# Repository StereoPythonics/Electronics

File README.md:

# Electronics
Schematics and PCBs for my electronics projects.

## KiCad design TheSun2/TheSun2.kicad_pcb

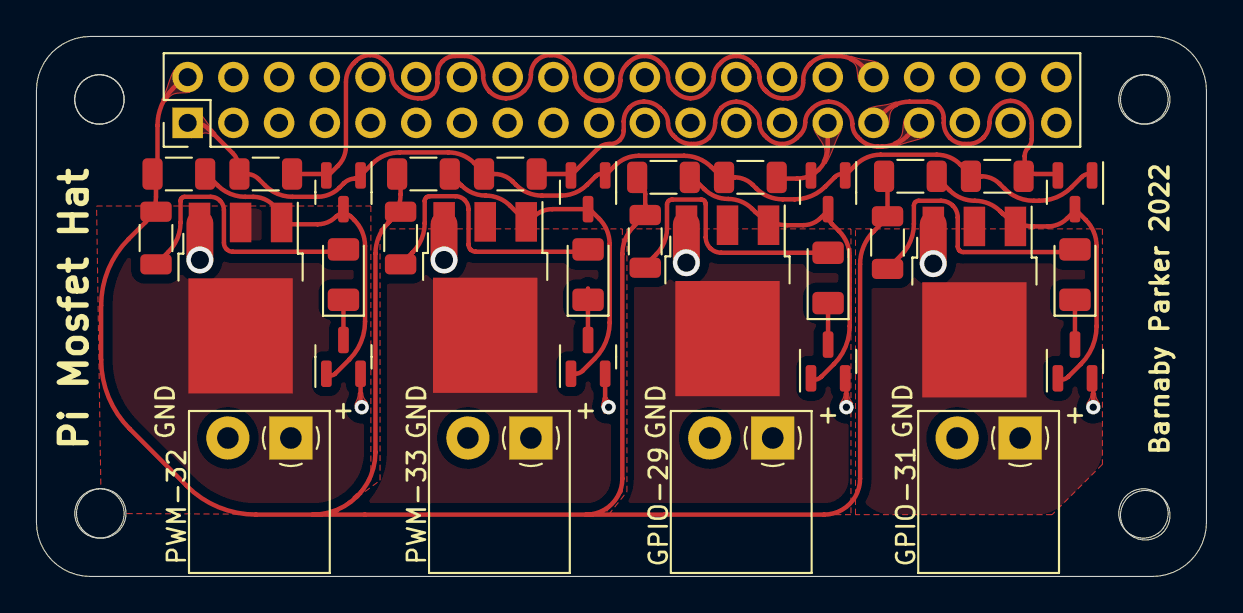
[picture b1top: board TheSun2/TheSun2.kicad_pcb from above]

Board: 2 copper layers, 65.0 x 30.0 mm, 33 parts (0 on the bottom side), 23 nets.

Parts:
D1, D2, D3, D4: LED; LED_1206_3216Metric
GPIO-29, GPIO-31: Screw_Terminal_01x02; TerminalBlock_4Ucon_1x02_P3.50mm_Horizontal
J5: Conn_02x20_Odd_Even; PinHeader_2x20_P2.54mm_Vertical
PWM-32, PWM-33: Screw_Terminal_01x02; TerminalBlock_4Ucon_1x02_P3.50mm_Horizontal
Q1, Q2, Q3, Q4: IRLR7843; TO-252-3_TabPin2
R1, R3, R4, R6, R7, R9, R10, R12: 10K; R_1206_3216Metric
R2, R5, R8, R11: 500R; R_1206_3216Metric
U1, U2, U3, U4, U5, U6, U7, U8: 2N7002H; SOT-23

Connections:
3.3v: J5.1, R1.1, R4.1, R7.1, R10.1, U1.1 (G), U2.1 (G), U5.1 (G), U6.1 (G)
5v: J5.2, R2.1, R3.2, R5.1, R6.2, R8.1, R9.2, R11.1, R12.2
/GPIO-29: J5.29, R4.2, U2.2 (S)
/GPIO-31: J5.31, R10.2, U6.2 (S)
/PWM-32: J5.32, R1.2, U1.2 (S)
/PWM-33: J5.33, R7.2, U5.2 (S)
GND: GPIO-29.2, GPIO-31.2, J5.6, J5.9, J5.14, J5.20, J5.25, J5.30, J5.34, J5.39, PWM-32.2, PWM-33.2, Q1.3 (S), Q2.3 (S), Q3.3 (S), Q4.3 (S), U3.2 (S), U4.2 (S), U7.2 (S), U8.2 (S)
unnamed: D1.1 (K), U3.3 (D)
unnamed: D1.2 (A), R2.2
unnamed: D2.1 (K), U4.3 (D)
unnamed: D2.2 (A), R5.2
unnamed: D3.1 (K), U7.3 (D)
unnamed: D3.2 (A), R8.2
unnamed: D4.1 (K), U8.3 (D)
unnamed: D4.2 (A), R11.2
unnamed: PWM-32.1, Q1.2 (D)
unnamed: GPIO-29.1, Q2.2 (D)
unnamed: PWM-33.1, Q3.2 (D)
unnamed: GPIO-31.1, Q4.2 (D)
unnamed: Q1.1 (G), R3.1, U1.3 (D), U3.1 (G)
unnamed: Q2.1 (G), R6.1, U2.3 (D), U4.1 (G)
unnamed: Q3.1 (G), R9.1, U5.3 (D), U7.1 (G)
unnamed: Q4.1 (G), R12.1, U6.3 (D), U8.1 (G)

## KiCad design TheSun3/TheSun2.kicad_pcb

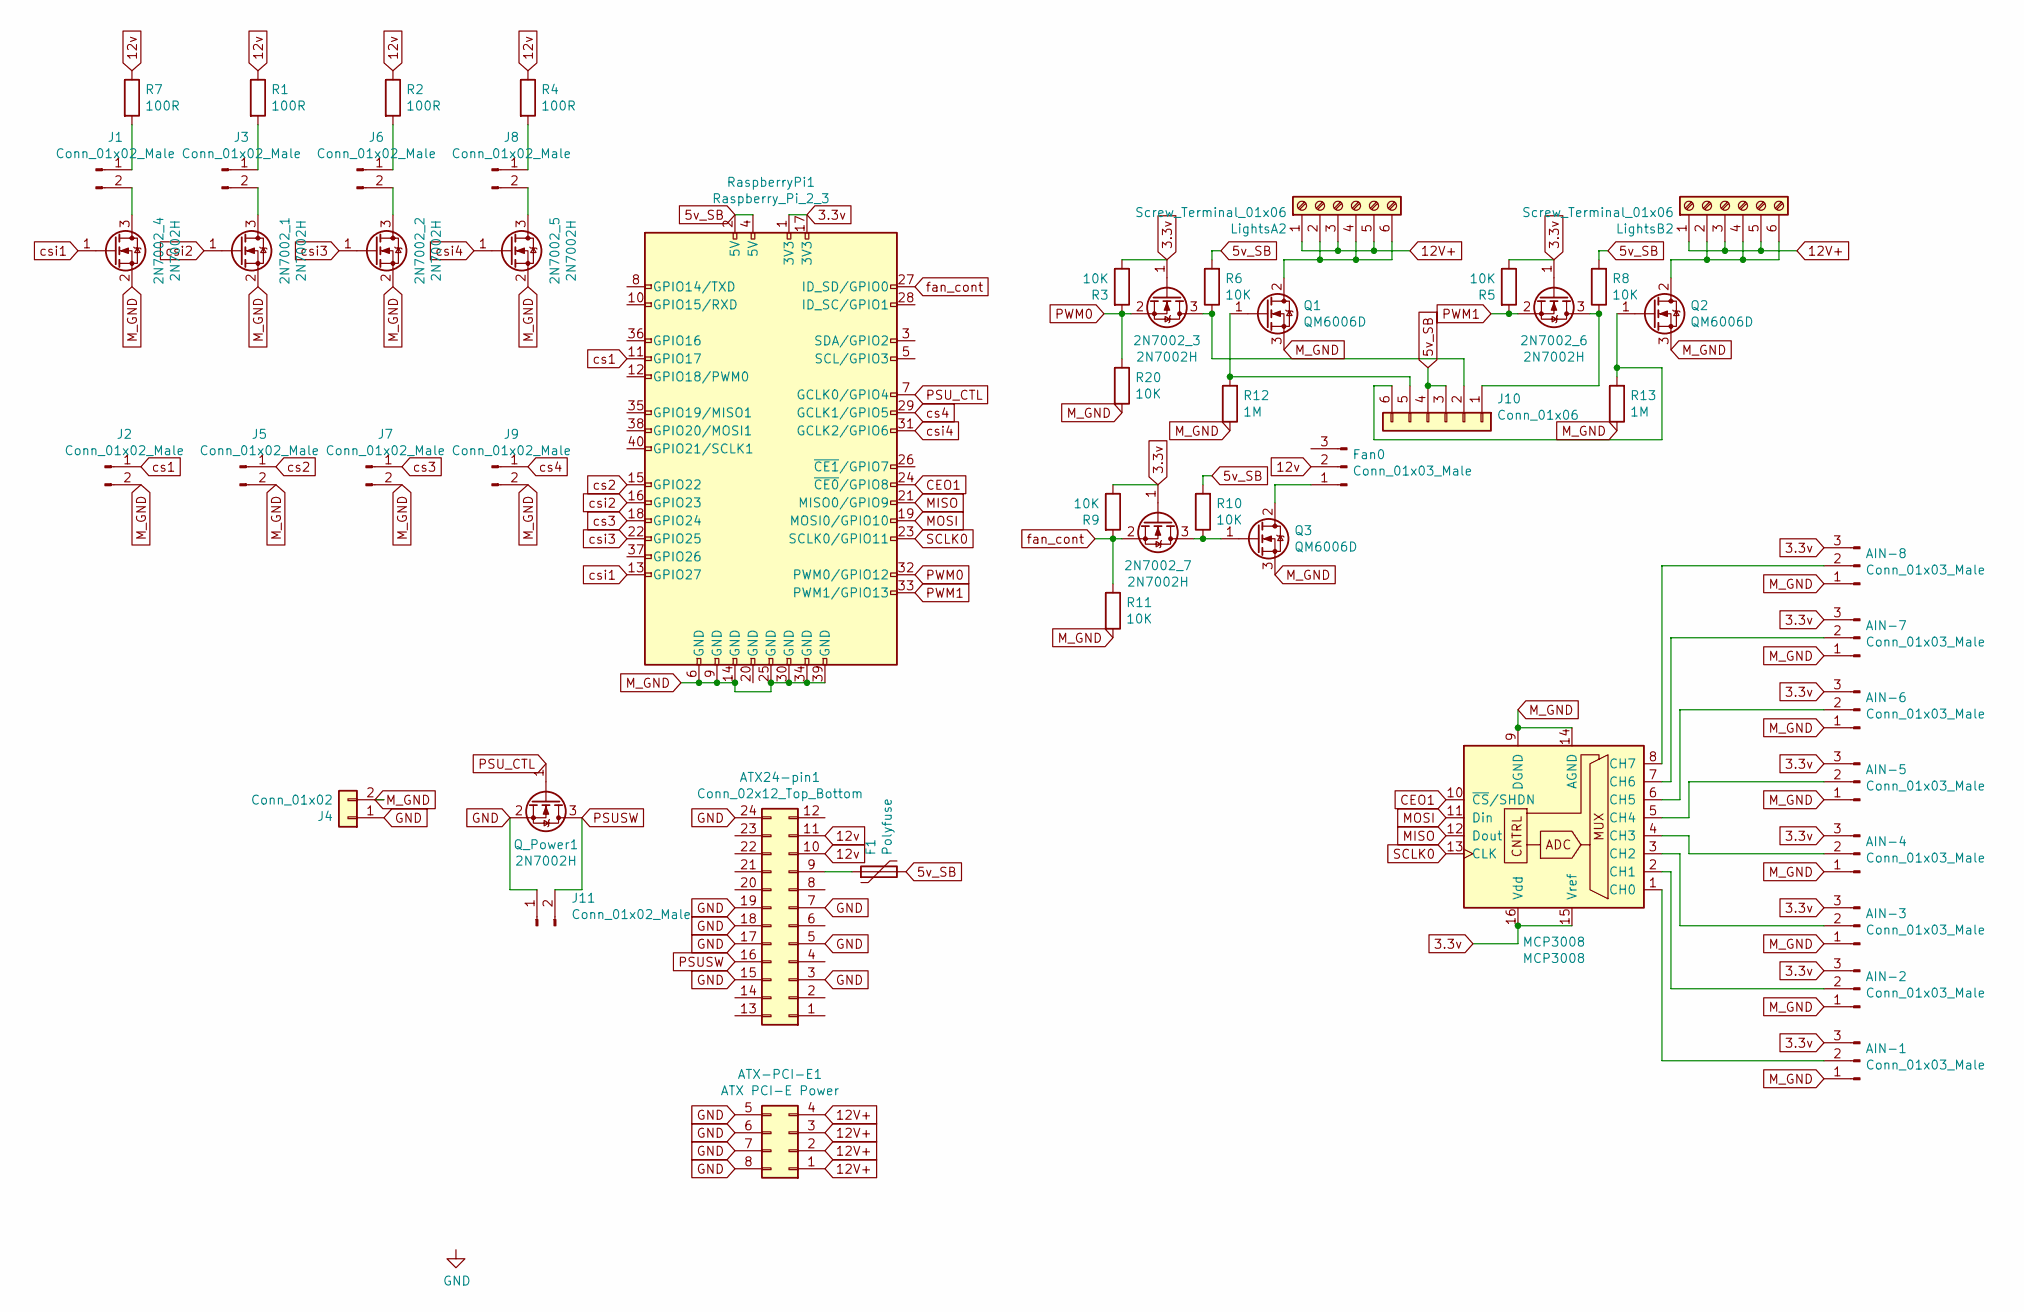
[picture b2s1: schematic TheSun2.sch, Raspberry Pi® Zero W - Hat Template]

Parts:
2N7002_1, 2N7002_2, 2N7002_3, 2N7002_4, 2N7002_5, 2N7002_6, 2N7002_7: 2N7002H; SOT-23
AIN-1, AIN-2, AIN-3, AIN-4, AIN-5, AIN-6, AIN-7, AIN-8: Conn_01x03_Male; PinHeader_1x03_P2.54mm_Vertical
ATX24-pin1: Conn_02x12_Top_Bottom; ATX_24pin
ATX-PCI-E1: ATX PCI-E Power; Molex_PCI_E_8Pin
F1: Polyfuse; R_1206_3216Metric_Pad1.30x1.75mm_HandSolder
Fan0: Conn_01x03_Male; PinHeader_1x03_P2.54mm_Vertical
J1, J2, J3, J5, J6, J7, J8, J9, J11: Conn_01x02_Male; PinHeader_1x02_P2.54mm_Vertical
J4: Conn_01x02; AMASS_XT60-M_1x02_P7.20mm_Vertical
J10: Conn_01x06; PinSocket_2x03_P2.54mm_Vertical
LightsA2: Screw_Terminal_01x06; PhoenixContact_MCV_1,5_6-G-3.81_1x06_P3.81mm_Vertical
LightsB2: Screw_Terminal_01x06; PhoenixContact_MCV_1,5_6-G-3.81_1x06_P3.81mm_Vertical
MCP3008: MCP3008; SOIC-16_3.9x9.9mm_P1.27mm
Q1, Q2, Q3: QM6006D; TO-252-2
Q_Power1: 2N7002H; SOT-23
R1, R2, R4, R7: 100R; R_1206_3216Metric_Pad1.30x1.75mm_HandSolder
R3, R5, R6, R8, R9, R10, R11, R20: 10K; R_1206_3216Metric_Pad1.30x1.75mm_HandSolder
R12, R13: 1M; R_1206_3216Metric_Pad1.30x1.75mm_HandSolder
RaspberryPi1: Raspberry_Pi_2_3; PinHeader_2x20_P2.54mm_Vertical

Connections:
3.3v: 2N7002_3.1 (G), 2N7002_6.1 (G), 2N7002_7.1 (G), AIN-1.3, AIN-2.3, AIN-3.3, AIN-4.3, AIN-5.3, AIN-6.3, AIN-7.3, AIN-8.3, MCP3008.15 (Vref), MCP3008.16 (Vdd), R3.1, R5.1, R9.1, RaspberryPi1.1 (3V3), RaspberryPi1.17 (3V3)
5v_SB: F1.2, J10.3, J10.4, R6.2, R8.2, R10.2, RaspberryPi1.2 (5V), RaspberryPi1.4 (5V)
12V+: ATX-PCI-E1.1, ATX-PCI-E1.2, ATX-PCI-E1.3, ATX-PCI-E1.4, LightsA2.1, LightsA2.3, LightsA2.5, LightsB2.1, LightsB2.3, LightsB2.5
12v: ATX24-pin1.10, ATX24-pin1.11, Fan0.2, R1.1, R2.1, R4.1, R7.1
CEO1: MCP3008.10 (~CS~/SHDN), RaspberryPi1.24 (~CE0~/GPIO8)
GND: ATX24-pin1.3, ATX24-pin1.5, ATX24-pin1.7, ATX24-pin1.15, ATX24-pin1.17, ATX24-pin1.18, ATX24-pin1.19, ATX24-pin1.24, ATX-PCI-E1.5, ATX-PCI-E1.6, ATX-PCI-E1.7, ATX-PCI-E1.8, J4.1, J11.1, Q_Power1.2 (S); also elsewhere on the board
MISO: MCP3008.12 (Dout), RaspberryPi1.21 (MISO0/GPIO9)
MOSI: MCP3008.11 (Din), RaspberryPi1.19 (MOSI0/GPIO10)
M_GND: 2N7002_1.2 (S), 2N7002_2.2 (S), 2N7002_4.2 (S), 2N7002_5.2 (S), AIN-1.1, AIN-2.1, AIN-3.1, AIN-4.1, AIN-5.1, AIN-6.1, AIN-7.1, AIN-8.1, J2.2, J4.2, J5.2, J7.2, J9.2, MCP3008.9 (DGND), MCP3008.14 (AGND), Q1.3 (S), Q2.3 (S), Q3.3 (S), R11.2, R12.1, R13.1, R20.2, RaspberryPi1.6 (GND), RaspberryPi1.9 (GND), RaspberryPi1.14 (GND), RaspberryPi1.25 (GND), RaspberryPi1.30 (GND), RaspberryPi1.34 (GND), RaspberryPi1.39 (GND)
unnamed: 2N7002_1.3 (D), J3.2
unnamed: 2N7002_2.3 (D), J6.2
unnamed: 2N7002_3.3 (D), J10.2, R6.1
unnamed: 2N7002_4.3 (D), J1.2
unnamed: 2N7002_5.3 (D), J8.2
unnamed: 2N7002_6.3 (D), J10.1, R8.1
unnamed: 2N7002_7.3 (D), Q3.1 (G), R10.1
unnamed: AIN-1.2, MCP3008.1 (CH0)
unnamed: AIN-2.2, MCP3008.2 (CH1)
unnamed: AIN-3.2, MCP3008.3 (CH2)
unnamed: AIN-4.2, MCP3008.4 (CH3)
unnamed: AIN-5.2, MCP3008.5 (CH4)
unnamed: AIN-6.2, MCP3008.6 (CH5)
unnamed: AIN-7.2, MCP3008.7 (CH6)
unnamed: AIN-8.2, MCP3008.8 (CH7)
unnamed: ATX24-pin1.9, F1.1
unnamed: Fan0.1, Q3.2 (D)
unnamed: J1.1, R7.2
unnamed: J3.1, R1.2
unnamed: J6.1, R2.2
unnamed: J8.1, R4.2
unnamed: J10.5, Q1.1 (G), R12.2
unnamed: J10.6, Q2.1 (G), R13.2
unnamed: LightsA2.2, LightsA2.4, LightsA2.6, Q1.2 (D)
unnamed: LightsB2.2, LightsB2.4, LightsB2.6, Q2.2 (D)
PSUSW: ATX24-pin1.16, J11.2, Q_Power1.3 (D); also elsewhere on the board
PSU_CTL: Q_Power1.1 (G), RaspberryPi1.7 (GCLK0/GPIO4)
PWM0: 2N7002_3.2 (S), R3.2, R20.1, RaspberryPi1.32 (PWM0/GPIO12)
PWM1: 2N7002_6.2 (S), R5.2, RaspberryPi1.33 (PWM1/GPIO13)
SCLK0: MCP3008.13 (CLK), RaspberryPi1.23 (SCLK0/GPIO11)
cs1: J2.1, RaspberryPi1.11 (GPIO17)
cs2: J5.1, RaspberryPi1.15 (GPIO22)
cs3: J7.1, RaspberryPi1.18 (GPIO24)
cs4: J9.1, RaspberryPi1.29 (GCLK1/GPIO5)
csi1: 2N7002_4.1 (G), RaspberryPi1.13 (GPIO27)
csi2: 2N7002_1.1 (G), RaspberryPi1.16 (GPIO23)
csi3: 2N7002_2.1 (G), RaspberryPi1.22 (GPIO25)
csi4: 2N7002_5.1 (G), RaspberryPi1.31 (GCLK2/GPIO6)
fan_cont: 2N7002_7.2 (S), R9.2, R11.1, RaspberryPi1.27 (ID_SD/GPIO0)

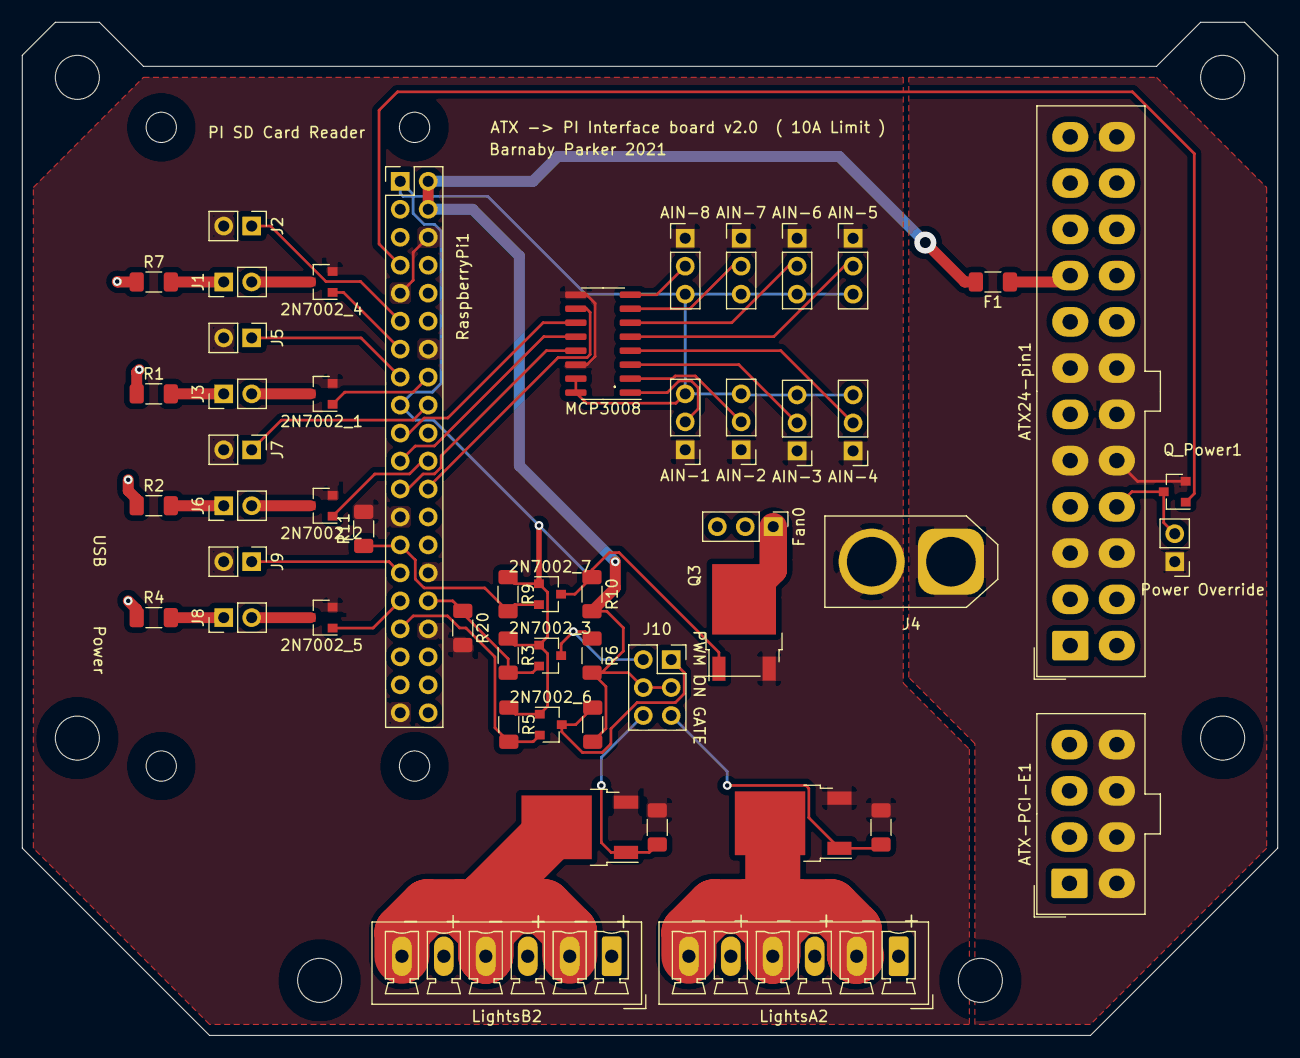
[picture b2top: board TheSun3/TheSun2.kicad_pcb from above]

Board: 2 copper layers, 114.0 x 92.0 mm, 52 parts (0 on the bottom side), 48 nets.

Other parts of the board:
Power Override: Conn_01x02_Male; PinHeader_1x02_P2.54mm_Vertical

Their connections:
GND: Power Override.1; also elsewhere on the board
PSUSW: Power Override.2; also elsewhere on the board

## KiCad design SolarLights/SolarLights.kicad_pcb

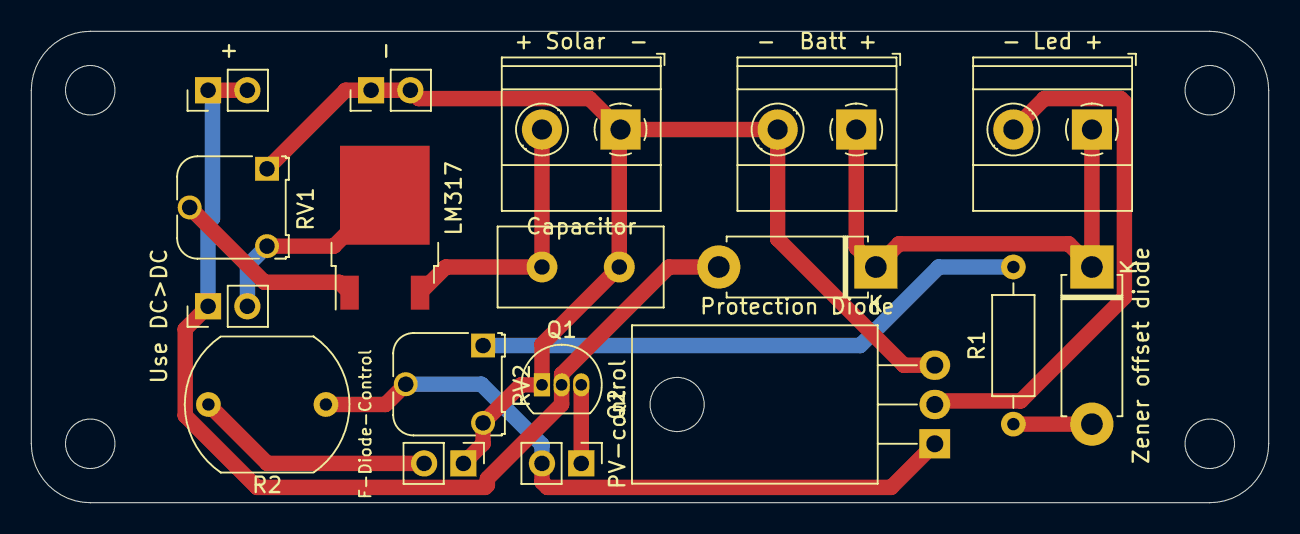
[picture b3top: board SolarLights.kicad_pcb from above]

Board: 2 copper layers, 80.0 x 30.5 mm, 22 parts (0 on the bottom side), 12 nets.

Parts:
 : MountingHole_3.2mm_M3
 #2,  #3,  #4: MountingHole_3.2mm_M3
+: dc->dc +; PinHeader_1x02_P2.54mm_Vertical
+ Solar  -: C; C_Disc_D10.5mm_W5.0mm_P5.00mm
-: dc->dc -; PinHeader_1x02_P2.54mm_Vertical
-  Batt +: Battery Terminal; TerminalBlock_Phoenix_MKDS-1,5-2-5.08_1x02_P5.08mm_Horizont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
- Led +: Led Terminal; TerminalBlock_Phoenix_MKDS-1,5-2-5.08_1x02_P5.08mm_Horizont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
Capacitor: Solar; TerminalBlock_Phoenix_MKDS-1,5-2-5.08_1x02_P5.08mm_Horizont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
F-Diode-Control: Jumper; PinHeader_1x02_P2.54mm_Vertical
LM317: LM317_TO-252; TO-252-2
PV-control: Jumper; PinHeader_1x02_P2.54mm_Vertical
Protection Diode: D; D_5W_P10.16mm_Horizontal
Q1: 2N7000; TO-92_Inline
Q2: IRLZ44N; TO-220-3_Horizontal_TabDown
R1: R; R_Axial_DIN0207_L6.3mm_D2.5mm_P10.16mm_Horizontal
R2: LDR03; R_LDR_10x8.5mm_P7.6mm_Vertical
RV1, RV2: R_POT; Potentiometer_Runtron_RM-065_Vertical
Use DC>DC: Jumper; PinHeader_1x02_P2.54mm_Vertical
Zener offset diode: D_Zener; D_5W_P10.16mm_Horizontal

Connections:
unnamed: + Solar -.1, Capacitor.2, LM317.3
unnamed: + Solar -.2, -.1, -.2, - Batt +.2, Capacitor.1, F-Diode-Control.1, Q1.1, Q2.3, RV1.1, RV2.3
unnamed: - Batt +.1, - Led +.1, Protection Diode.1, Zener offset diode.1
unnamed: +.1, +.2, Protection Diode.2, Q1.2, Use DC>DC.1
unnamed: R1.1, Zener offset diode.2
unnamed: LM317.2, RV1.3, Use DC>DC.2
unnamed: - Led +.2, Q2.2
unnamed: F-Diode-Control.2, R2.2
unnamed: PV-control.1, Q1.3
unnamed: PV-control.2, Q2.1, R2.1, RV2.2
unnamed: R1.2, RV2.1
unnamed: LM317.1, RV1.2

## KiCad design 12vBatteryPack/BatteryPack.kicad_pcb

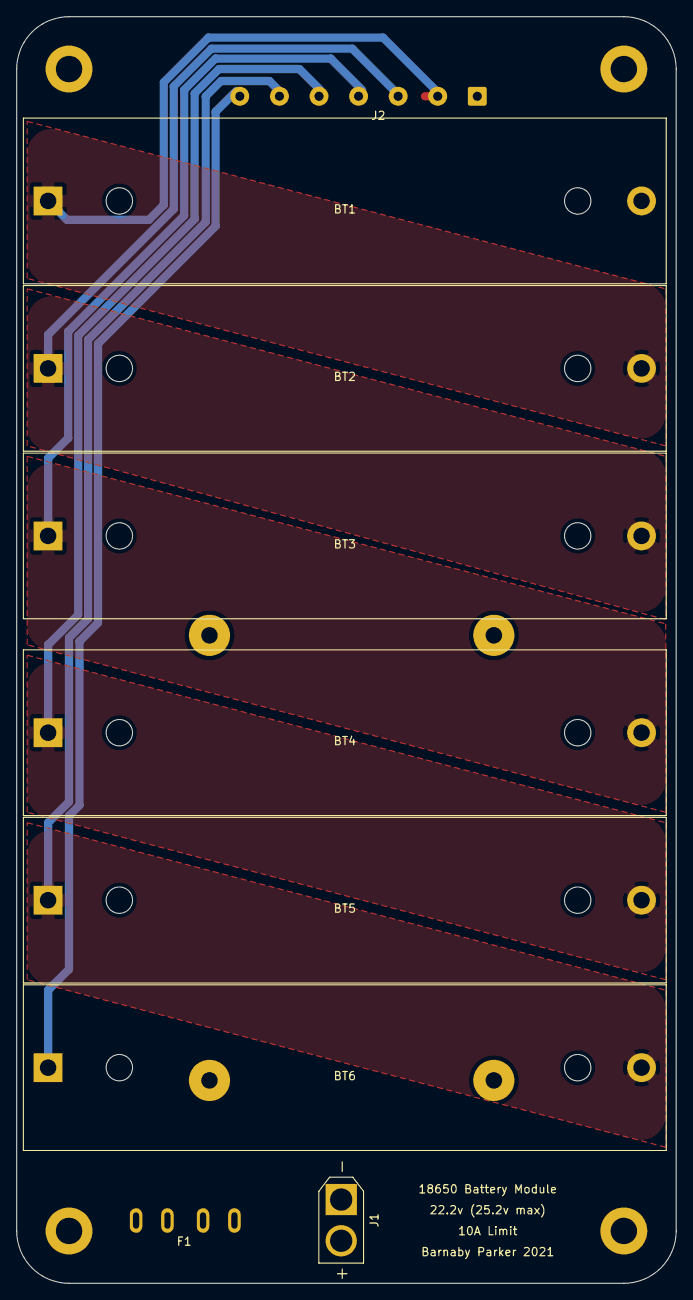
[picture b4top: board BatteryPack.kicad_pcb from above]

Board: 2 copper layers, 80.0 x 153.7 mm, 10 parts (1 on the bottom side), 9 nets.

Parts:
BT1, BT2, BT3, BT4, BT5, BT6: Battery_Cell; BatteryHolder_MPD_BH-18650-PC2
F1: Fuse; Spade Fuse Holder
J1: Conn_01x02_Male; AMASS_XT30U-M_1x02_P5.0mm_Vertical
J2: Conn_01x07_Male; SolderWire-0.5sqmm_1x07_P4.8mm_D0.9mm_OD2.3mm
J3: Conn_01x02_Male; BMS_Board

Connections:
BAT+: BT6.1, F1.1, J2.7
BAT-: BT1.2, J2.1, J3.2
BAT_BAL1: BT1.1, BT2.2, J2.2
BAT_BAL2: BT2.1, BT3.2, J2.3
BAT_BAL3: BT3.1, BT4.2, J2.4
BAT_BAL4: BT4.1, BT5.2, J2.5
BAT_BAL5: BT5.1, BT6.2, J2.6
BMS_Source: J1.1, J3.1
unnamed: F1.2, J1.2

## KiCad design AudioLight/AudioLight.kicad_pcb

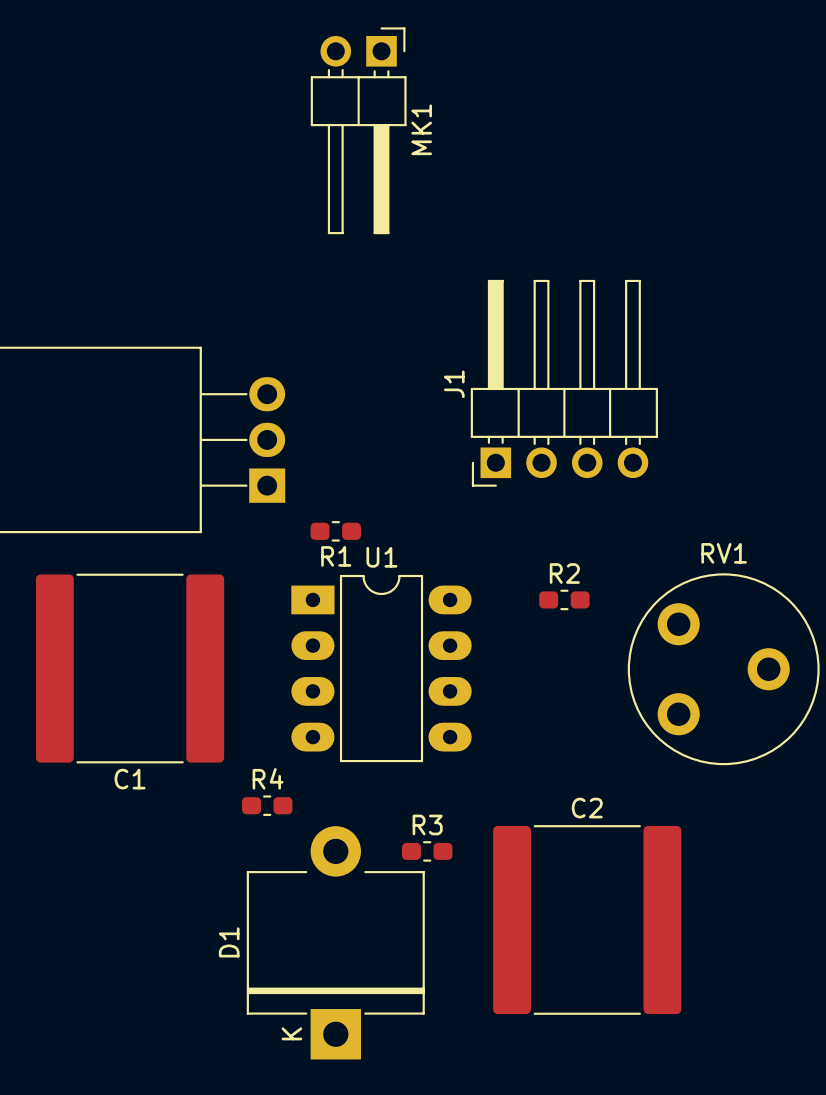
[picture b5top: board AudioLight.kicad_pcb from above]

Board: 2 copper layers, 12 parts (0 on the bottom side), 10 nets, no tracks yet.

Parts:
C1, C2: C; C_3640_9110Metric_Pad2.10x10.45mm_HandSolder
D1: D; D_5KP_P10.16mm_Horizontal
J1: Conn_01x04_Male; PinHeader_1x04_P2.54mm_Horizontal
MK1: Microphone_Condenser; PinHeader_1x02_P2.54mm_Horizontal
Q1: IRLZ44N; TO-220-3_Horizontal_TabDown
R1, R2, R3, R4: R; R_0603_1608Metric_Pad1.05x0.95mm_HandSolder
RV1: R_POT_TRIM; Potentiometer_Piher_PT-10-V05_Vertical
U1: LM741; DIP-8_W7.62mm_LongPads

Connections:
unnamed: C1.1, U1.3
unnamed: C1.2, MK1.2, R1.2
unnamed: C2.1, D1.1, Q1.1, R4.1
unnamed: C2.2, J1.3, MK1.1, Q1.3, R4.2, RV1.1, U1.4
unnamed: D1.2, R3.1
unnamed: J1.1, Q1.2
unnamed: J1.2, J1.4, R1.1, U1.7
unnamed: R2.1, R3.2, U1.6
unnamed: R2.2, RV1.3
unnamed: RV1.2, U1.2

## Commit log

2021-11-07 Added untracked projects
2022-01-05 Start of 12v battery pack and start of embedded dip8 concept
2022-01-05 Included an export of embedded dip8 footprint
2022-10-21 Added more existing projects
2022-10-22 Added fancy pi power mosfet hat
2022-10-22 Added silkscreening
2022-10-26 Added first draft for pi mosfethat
